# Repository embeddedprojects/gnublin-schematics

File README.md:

gnublin-schematics
==================

GNUBLIN Schematic and Board Files

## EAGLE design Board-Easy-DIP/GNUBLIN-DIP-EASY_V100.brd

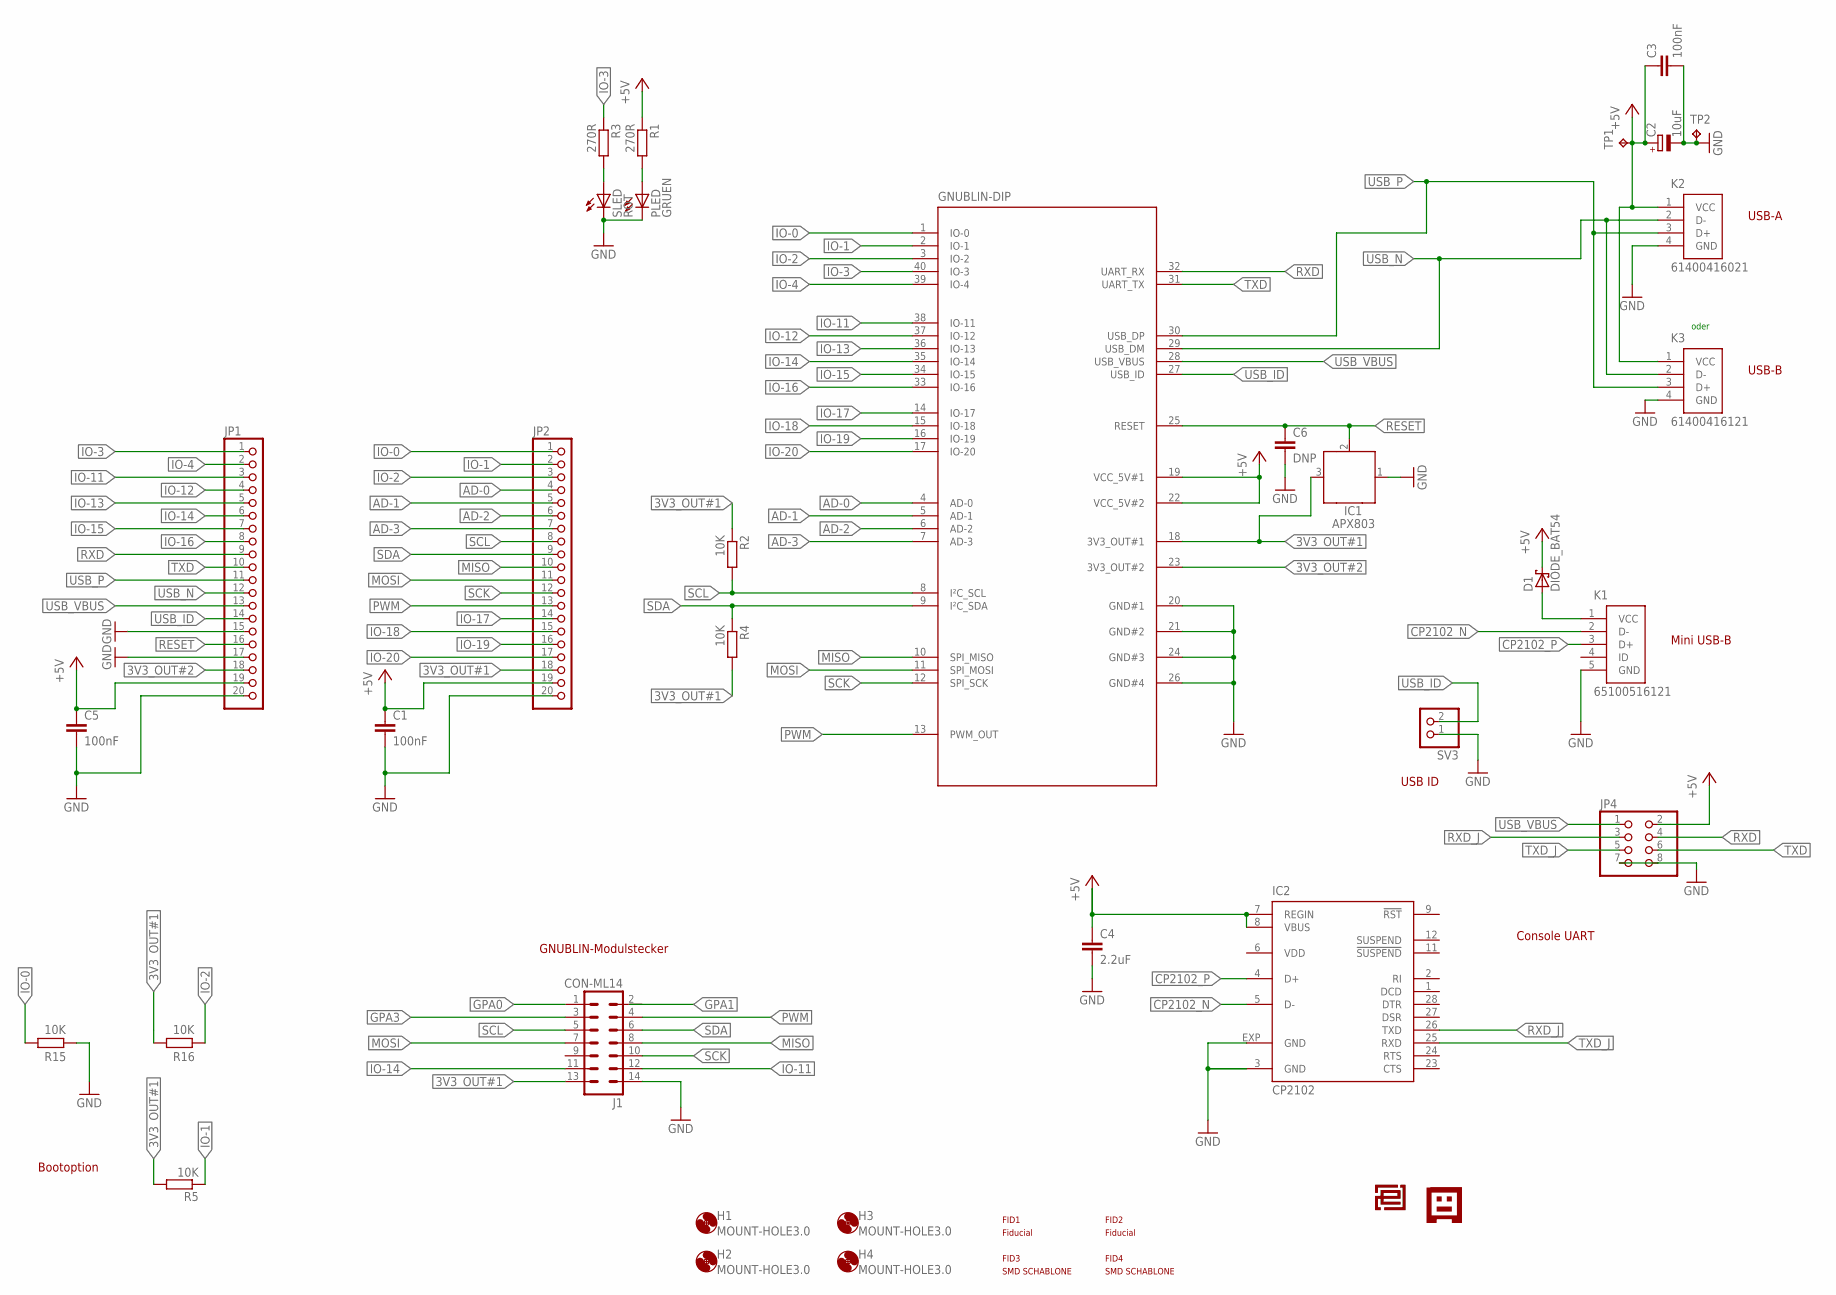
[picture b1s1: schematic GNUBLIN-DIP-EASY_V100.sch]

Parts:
C1, C3, C5: 100nF; C0805
C2: 10uF; D/7343-31R
C4: 2.2uF; C0805
C6: DNP; C0805
D1: DIODE_BAT54; SOT-23
FID1, FID2, FID3, FID4: PASSERMARKEN_FIDUCIAL
H1, H2, H3, H4: MOUNT-HOLE3.0; 3,0
IC1: APX803; SOT23
IC2: CP2102; MLP28
J1: CON-ML14; ML-14
JP1, JP2: PINHD-1X20; 1X20
JP4: PINHD-2X4; 2X04
K1: 65100516121
K2: 61400416021
K3: 61400416121
PLED: GRUEN; CHIPLED_0805
R1, R3: 270R; R0805
R2, R4, R5, R15, R16: 10K; R0805
SLED: ROT; CHIPLED_0805
SV3: PINHD-1X2; 1X02
TP1, TP2: TPB1,27; B1,27
U4: GNUBLIN-DIP; DIL40
U$1: GNUBLIN-LOGODRUCK; GNUBLINSIEBDRUCK
U$2: EPLOGOSIEB; EPLOGOSIEBDRUCK

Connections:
3V3_OUT#1: IC1.3 (VCC), J1.13, JP2.18, R2.1, R4.2, R5.2, R16.1, U4.18 (3V3_OUT#1)
3V3_OUT#2: JP1.18, U4.23 (3V3_OUT#2)
+5V: C1.1, C2.+, C3.1, C4.1, C5.1, D1.3 (C), IC2.7 (REGIN), IC2.8 (VBUS), JP1.19, JP2.19, JP4.2, K2.1 (VCC), K3.1 (VCC), R1.1, TP1.TP, U4.19 (VCC_5V#1), U4.22 (VCC_5V#2)
AD-0: JP2.4, U4.4 (AD-0)
AD-1: JP2.5, U4.5 (AD-1)
AD-2: JP2.6, U4.6 (AD-2)
AD-3: JP2.7, U4.7 (AD-3)
CP2102_N: IC2.5 (D-), K1.2 (D-)
CP2102_P: IC2.4 (D+), K1.3 (D+)
GND: C1.2, C2.-, C3.2, C4.2, C5.2, C6.2, IC1.1 (GND), IC2.3 (GND), IC2.EXP (GND), J1.14, JP1.15, JP1.17, JP1.20, JP2.20, JP4.7, JP4.8, K1.5 (GND), K2.4 (GND), K3.4 (GND), PLED.C, R15.2, SLED.C, SV3.1, TP2.TP, U4.20 (GND#1), U4.21 (GND#2), U4.24 (GND#3), U4.26 (GND#4)
GPA0: J1.1
GPA3: J1.3
IO-0: JP2.1, R15.1, U4.1 (IO-0)
IO-1: JP2.2, R5.1, U4.2 (IO-1)
IO-2: JP2.3, R16.2, U4.3 (IO-2)
IO-3: JP1.1, R3.1, U4.40 (IO-3)
IO-4: JP1.2, U4.39 (IO-4)
IO-11: J1.12, JP1.3, U4.38 (IO-11)
IO-12: JP1.4, U4.37 (IO-12)
IO-13: JP1.5, U4.36 (IO-13)
IO-14: J1.11, JP1.6, U4.35 (IO-14)
IO-15: JP1.7, U4.34 (IO-15)
IO-16: JP1.8, U4.33 (IO-16)
IO-17: JP2.14, U4.14 (IO-17)
IO-18: JP2.15, U4.15 (IO-18)
IO-19: JP2.16, U4.16 (IO-19)
IO-20: JP2.17, U4.17 (IO-20)
MISO: J1.8, JP2.10, U4.10 (SPI_MISO)
MOSI: J1.7, JP2.11, U4.11 (SPI_MOSI)
unnamed: R3.2, SLED.A
unnamed: D1.1 (A), K1.1 (VCC)
unnamed: PLED.A, R1.2
PWM: J1.4, JP2.13, U4.13 (PWM_OUT)
RESET: C6.1, IC1.2 (!RESET), JP1.16, U4.25 (RESET)
RXD: JP1.9, JP4.4, U4.32 (UART_RX)
RXD_J: IC2.26 (TXD), JP4.3
SCK: J1.10, JP2.12, U4.12 (SPI_SCK)
SCL: J1.5, JP2.8, R2.2, U4.8 (I²C_SCL)
SDA: J1.6, JP2.9, R4.1, U4.9 (I²C_SDA)
TXD: JP1.10, JP4.6, U4.31 (UART_TX)
TXD_J: IC2.25 (RXD), JP4.5
USB_ID: JP1.14, SV3.2, U4.27 (USB_ID)
USB_N: JP1.12, K2.2 (D-), K3.2 (D-), U4.29 (USB_DM)
USB_P: JP1.11, K2.3 (D+), K3.3 (D+), U4.30 (USB_DP)
USB_VBUS: JP1.13, JP4.1, U4.28 (USB_VBUS)
VDD: IC2.6 (VDD)

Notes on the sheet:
USB ID
Mini USB-B
USB-A
Bootoption
GNUBLIN-Modulstecker
Console UART
oder
USB-B

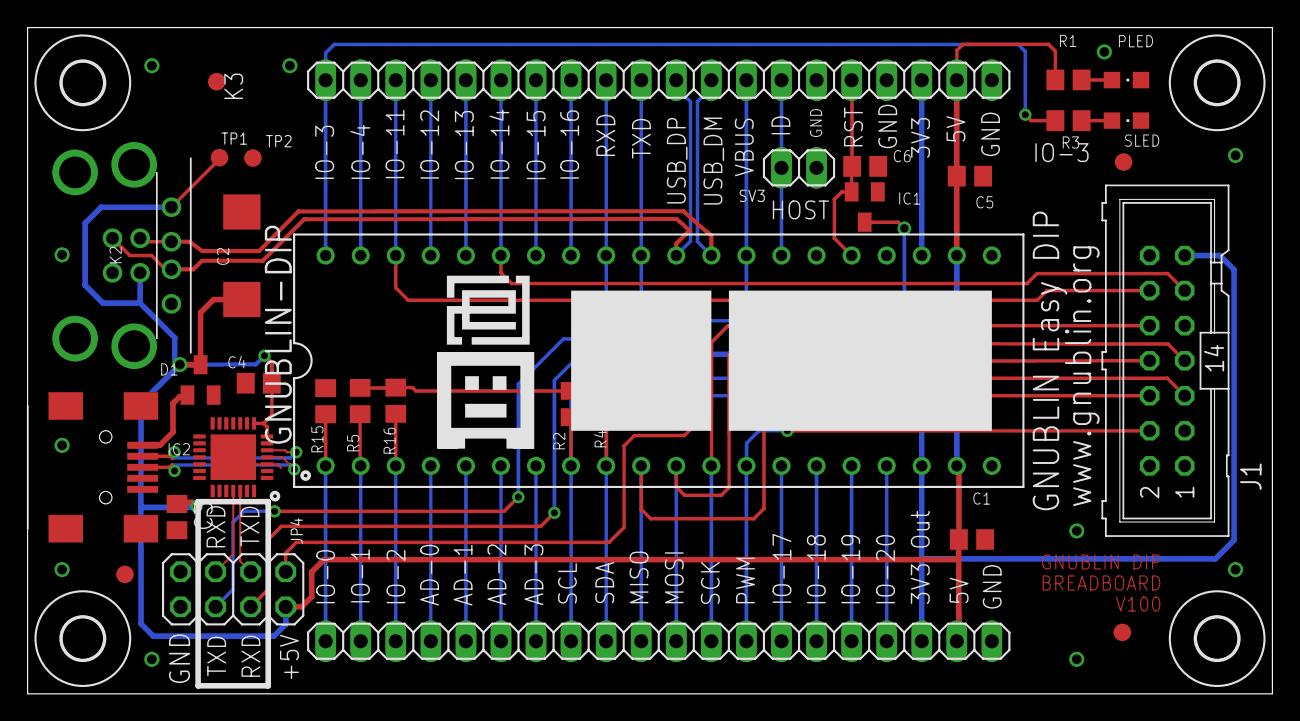
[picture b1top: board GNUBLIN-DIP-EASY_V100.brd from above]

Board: 2 copper layers, 90.2 x 48.3 mm, 39 parts (0 on the bottom side), 43 nets.

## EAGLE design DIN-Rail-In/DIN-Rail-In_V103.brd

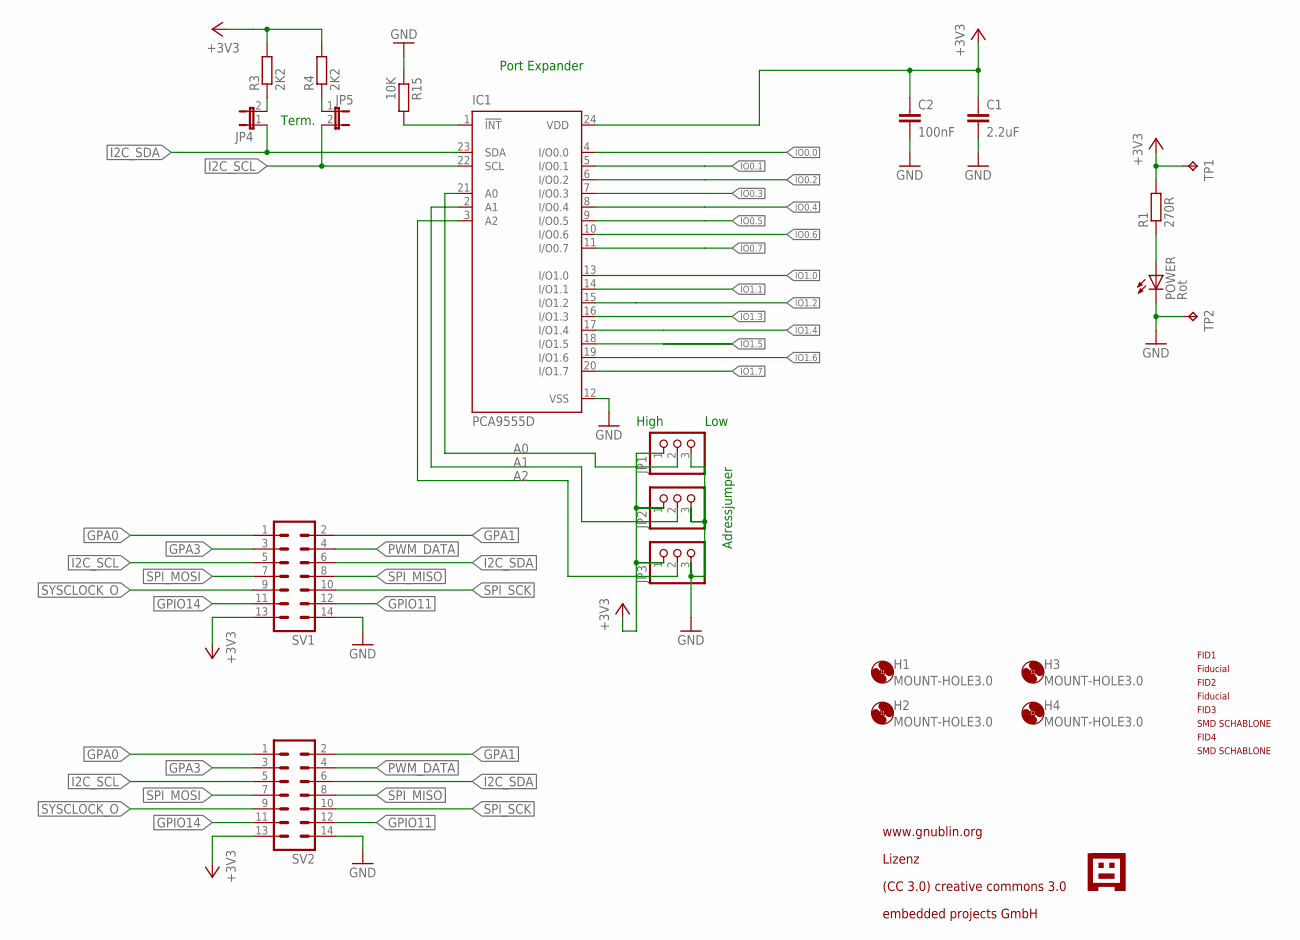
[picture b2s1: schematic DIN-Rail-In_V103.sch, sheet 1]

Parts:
C1: 2.2uF; C0805
C2: 100nF; C0805
FID1, FID2, FID3, FID4: PASSERMARKEN_FIDUCIAL
H1, H2, H3, H4: MOUNT-HOLE3.0; 3,0
IC1: PCA9555D; SO24
JP1, JP2, JP3: PINHD-1X3; 1X03
JP4, JP5: JP1E; JP1
POWER: Rot; CHIP-LED0805
R1: 270R; R0805
R3, R4: 2K2; R0805
R15: 10K; R0805
SV1, SV2: ML14
TP1, TP2: TPB1,27; B1,27
U$2: GNUBLINLOGOSIEB; GNUSIEBDRUCK

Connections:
!INT: IC1.1 (!INT), R15.2
+3V3: C1.1, C2.1, IC1.24 (VDD), JP1.1, JP2.1, JP3.1, R1.2, R3.2, R4.2, SV1.13, SV2.13, TP1.TP; also elsewhere on the board
A0: IC1.21 (A0), JP1.2
A1: IC1.2 (A1), JP2.2
A2: IC1.3 (A2), JP3.2
GND: C1.2, C2.2, IC1.12 (VSS), JP1.3, JP2.3, JP3.3, POWER.C, R15.1, SV1.14, SV2.14, TP2.TP; also elsewhere on the board
GPA0: SV1.1, SV2.1
GPA1: SV1.2, SV2.2
GPA3: SV1.3, SV2.3
GPIO11: SV1.12, SV2.12
GPIO14: SV1.11, SV2.11
I2C_SCL: IC1.22 (SCL), JP5.2, SV1.5, SV2.5
I2C_SDA: IC1.23 (SDA), JP4.1, SV1.6, SV2.6
IO0.0: IC1.4 (I/O0.0)
IO0.1: IC1.5 (I/O0.1)
IO0.2: IC1.6 (I/O0.2)
IO0.3: IC1.7 (I/O0.3)
IO0.4: IC1.8 (I/O0.4)
IO0.5: IC1.9 (I/O0.5)
IO0.6: IC1.10 (I/O0.6)
IO0.7: IC1.11 (I/O0.7)
IO1.0: IC1.13 (I/O1.0); also elsewhere on the board
IO1.1: IC1.14 (I/O1.1); also elsewhere on the board
IO1.2: IC1.15 (I/O1.2); also elsewhere on the board
IO1.3: IC1.16 (I/O1.3); also elsewhere on the board
IO1.4: IC1.17 (I/O1.4); also elsewhere on the board
IO1.5: IC1.18 (I/O1.5); also elsewhere on the board
IO1.6: IC1.19 (I/O1.6); also elsewhere on the board
IO1.7: IC1.20 (I/O1.7); also elsewhere on the board
unnamed: JP4.2, R3.1
unnamed: POWER.A, R1.1
unnamed: JP5.1, R4.1
PWM_DATA: SV1.4, SV2.4
SPI_MISO: SV1.8, SV2.8
SPI_MOSI: SV1.7, SV2.7
SPI_SCK: SV1.10, SV2.10
SYSCLOCK_O: SV1.9, SV2.9

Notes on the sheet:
Port Expander
Adressjumper
Term.
High
Low
www.gnublin.org
Lizenz
(CC 3.0) creative commons 3.0
embedded projects GmbH

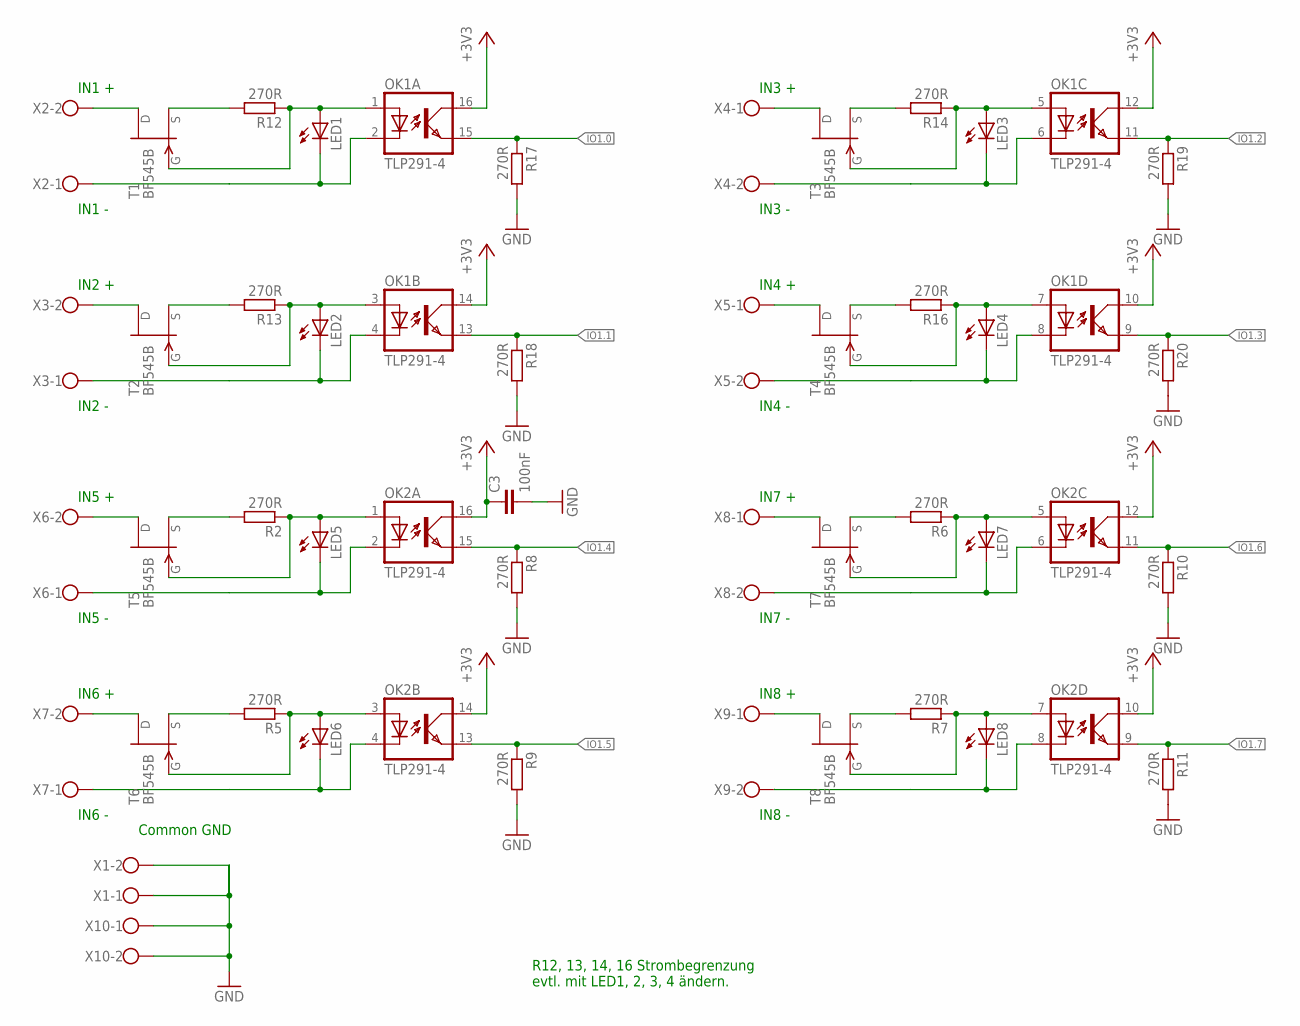
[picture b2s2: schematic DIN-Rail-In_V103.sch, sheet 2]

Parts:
C3: 100nF; C0805
LED1, LED2, LED3, LED4, LED5, LED6, LED7, LED8: LEDCHIPLED_0805; CHIPLED_0805
OK1, OK2: TLP291-4; MINI-FLAT-16
R2, R5, R6, R7, R8, R9, R10, R11, R12, R13, R14, R16, R17, R18, R19, R20: 270R; R0805
T1, T2, T3, T4, T5, T6, T7, T8: BF545B; SOT-23
X1, X2, X3, X4, X5, X6, X7, X8, X9, X10: W237-02P; W237-132

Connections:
+3V3: C3.1, OK1.10 (COL), OK1.12 (COL), OK1.14 (COL), OK1.16 (COL), OK2.10 (COL), OK2.12 (COL), OK2.14 (COL), OK2.16 (COL); also elsewhere on the board
GND: C3.2, R8.2, R9.2, R10.2, R11.2, R17.2, R18.2, R19.2, R20.2, X1.1, X1.2, X10.1, X10.2; also elsewhere on the board
IO1.0: OK1.15 (EMIT), R17.1; also elsewhere on the board
IO1.1: OK1.13 (EMIT), R18.1; also elsewhere on the board
IO1.2: OK1.11 (EMIT), R19.1; also elsewhere on the board
IO1.3: OK1.9 (EMIT), R20.1; also elsewhere on the board
IO1.4: OK2.15 (EMIT), R8.1; also elsewhere on the board
IO1.5: OK2.13 (EMIT), R9.1; also elsewhere on the board
IO1.6: OK2.11 (EMIT), R10.1; also elsewhere on the board
IO1.7: OK2.9 (EMIT), R11.1; also elsewhere on the board
unnamed: T1.2 (D), X2.2
unnamed: LED1.A, OK1.1 (A), R12.1, T1.3 (G)
unnamed: T5.2 (D), X6.2
unnamed: T2.2 (D), X3.2
unnamed: LED2.A, OK1.3 (A), R13.1, T2.3 (G)
unnamed: LED5.A, OK2.1 (A), R2.1, T5.3 (G)
unnamed: LED1.C, OK1.2 (C), X2.1
unnamed: T3.2 (D), X4.1
unnamed: LED3.A, OK1.5 (A), R14.1, T3.3 (G)
unnamed: T4.2 (D), X5.1
unnamed: LED4.A, OK1.7 (A), R16.1, T4.3 (G)
unnamed: T6.2 (D), X7.2
unnamed: LED2.C, OK1.4 (C), X3.1
unnamed: LED6.A, OK2.3 (A), R5.1, T6.3 (G)
unnamed: LED3.C, OK1.6 (C), X4.2
unnamed: LED4.C, OK1.8 (C), X5.2
unnamed: R12.2, T1.1 (S)
unnamed: T7.2 (D), X8.1
unnamed: R13.2, T2.1 (S)
unnamed: LED7.A, OK2.5 (A), R6.1, T7.3 (G)
unnamed: R14.2, T3.1 (S)
unnamed: T8.2 (D), X9.1
unnamed: R16.2, T4.1 (S)
unnamed: LED8.A, OK2.7 (A), R7.1, T8.3 (G)
unnamed: LED5.C, OK2.2 (C), X6.1
unnamed: LED6.C, OK2.4 (C), X7.1
unnamed: LED7.C, OK2.6 (C), X8.2
unnamed: LED8.C, OK2.8 (C), X9.2
unnamed: R2.2, T5.1 (S)
unnamed: R5.2, T6.1 (S)
unnamed: R6.2, T7.1 (S)
unnamed: R7.2, T8.1 (S)

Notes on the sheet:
IN1 +
IN1 -
IN2 +
IN2 -
IN3 +
IN3 -
IN4 +
IN4 -
Common GND
R12, 13, 14, 16 Strombegrenzung evtl. mit LED1, 2, 3, 4 ändern.
IN5 +
IN5 -
IN6 +
IN6 -
IN7 +
IN7 -
IN8 +
IN8 -

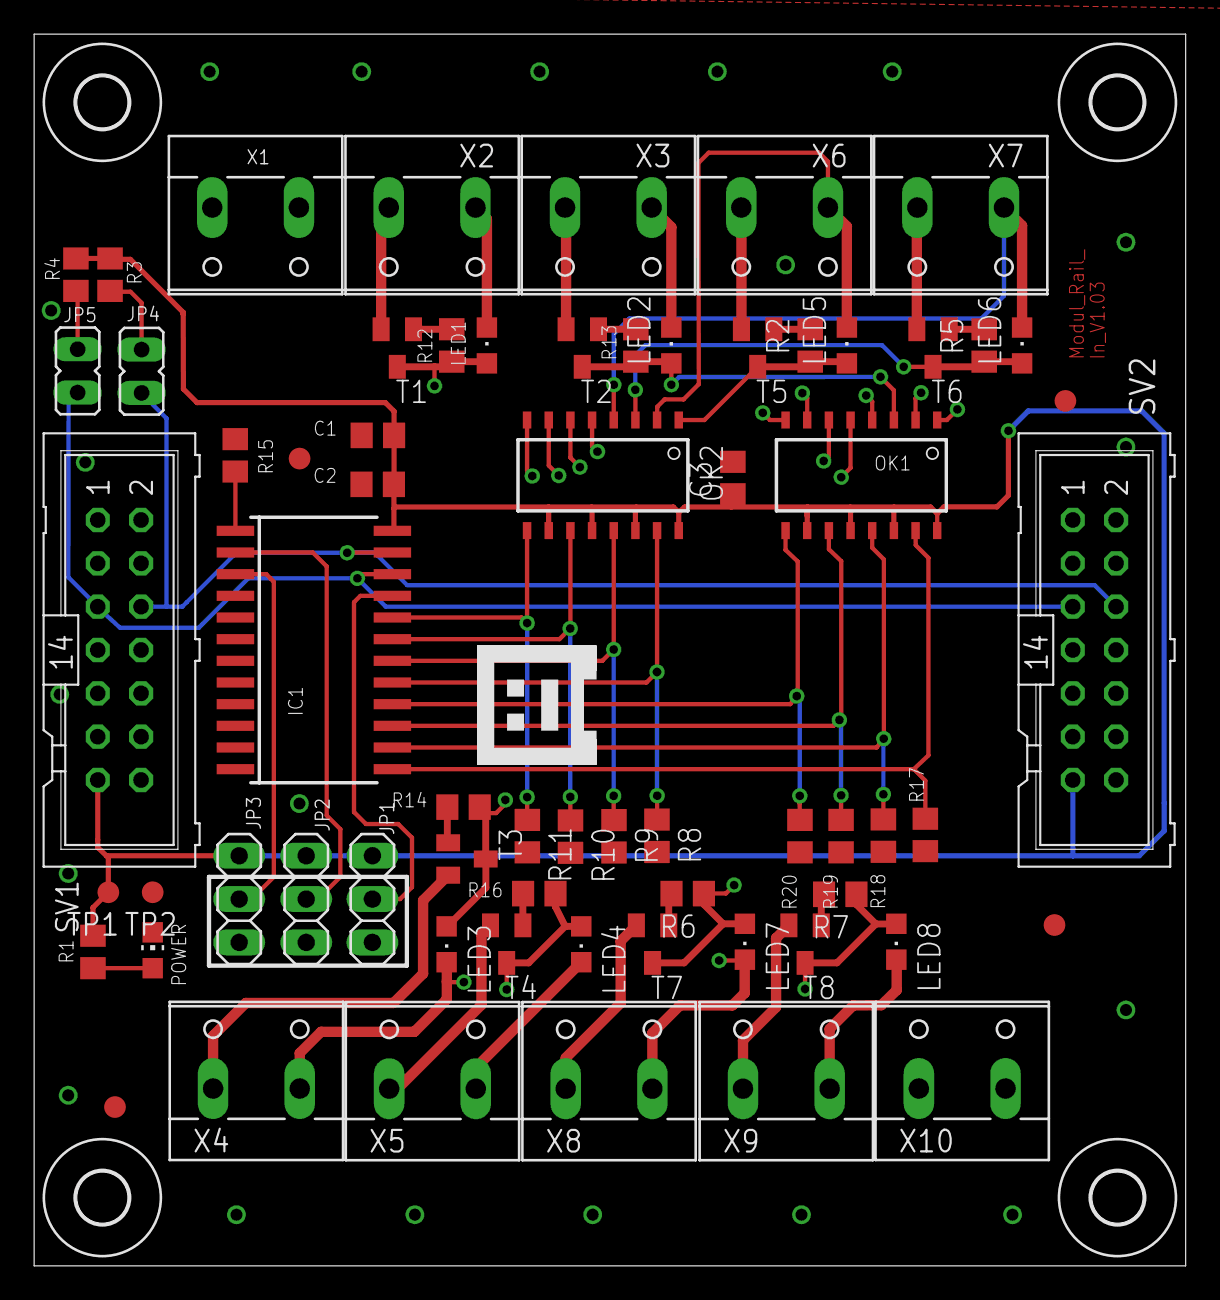
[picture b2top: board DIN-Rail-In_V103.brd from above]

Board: 4 copper layers, 67.5 x 72.2 mm, 71 parts (0 on the bottom side), 61 nets.

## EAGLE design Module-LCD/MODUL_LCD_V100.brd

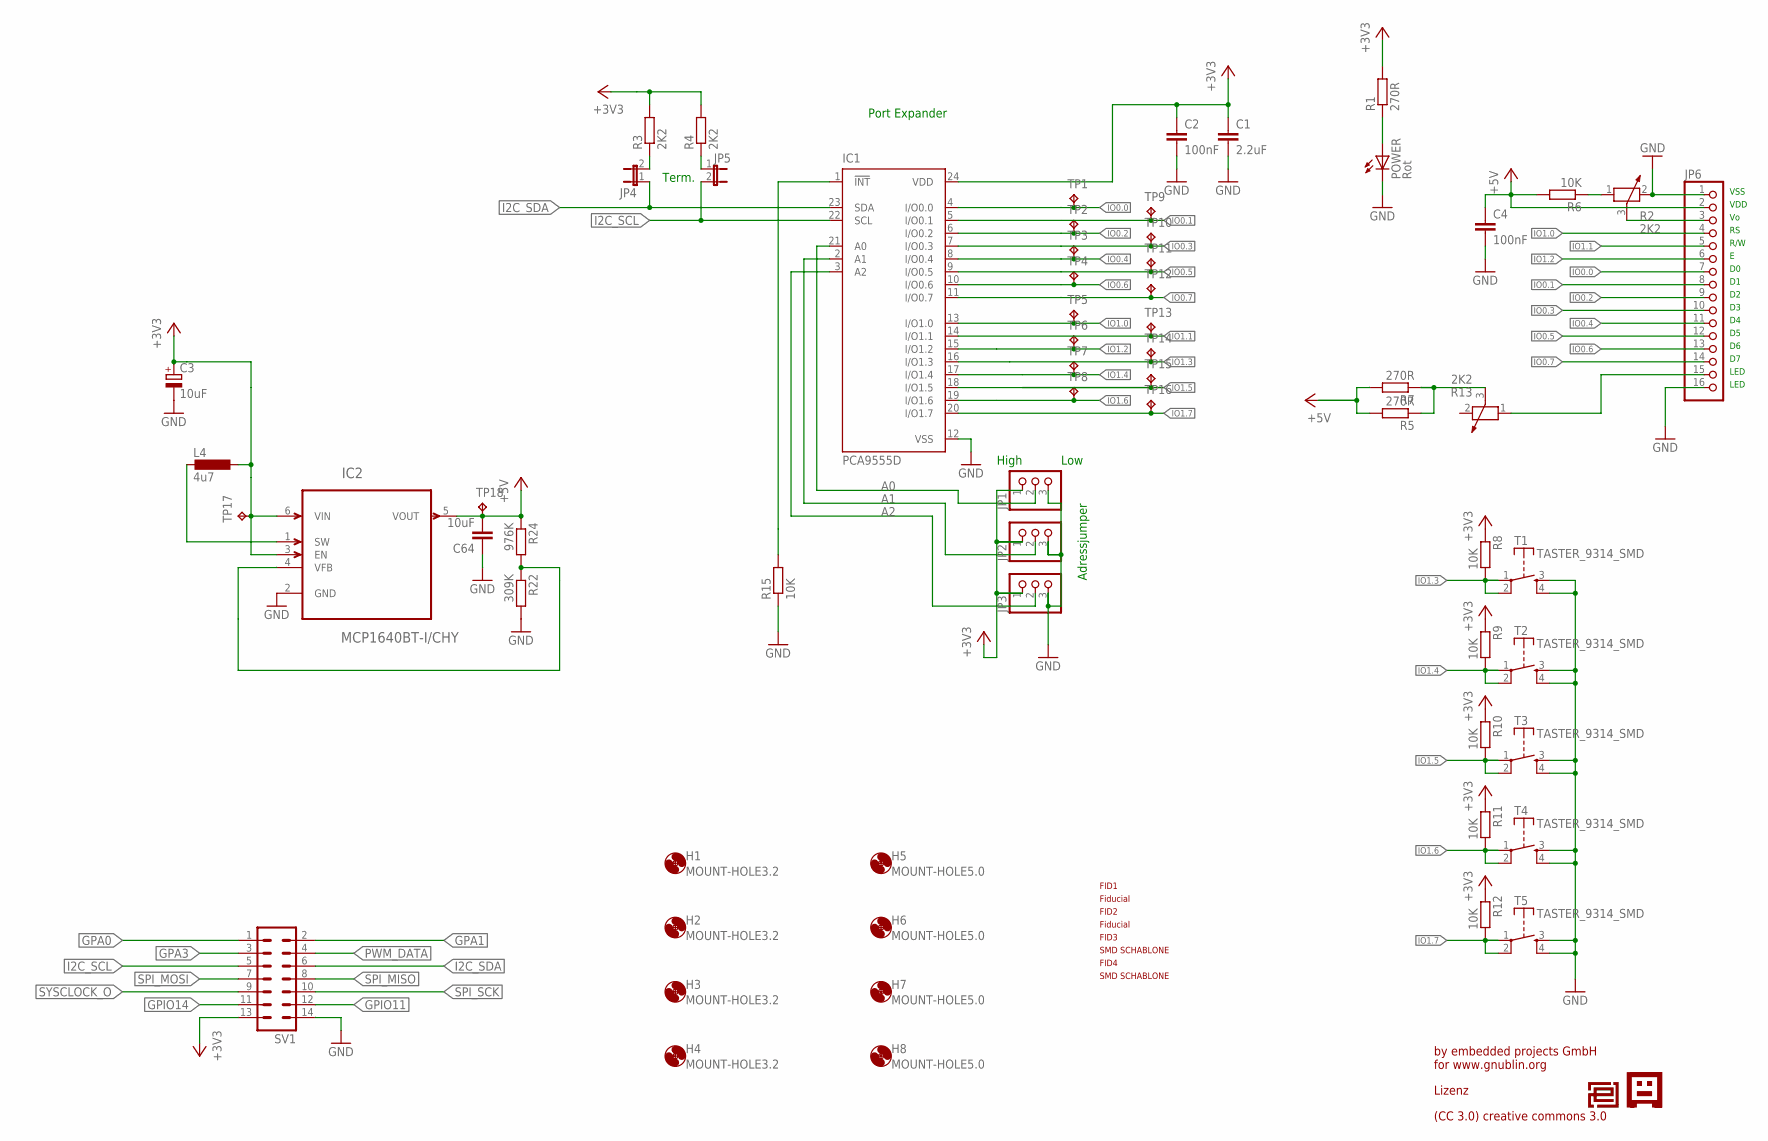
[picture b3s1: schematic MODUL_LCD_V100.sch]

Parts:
C1: 2.2uF; C0805
C2, C4: 100nF; C0805
C3: 10uF; SMC_D
C64: 10uF; C0805
FID1, FID2, FID3, FID4: PASSERMARKEN_FIDUCIAL
H1, H2, H3, H4: MOUNT-HOLE3.2; 3,2
H5, H6, H7, H8: MOUNT-HOLE5.0; 5,0
IC1: PCA9555D; SO24
IC2: MCP1640BT-I/CHY; SOT95P270X145-6N
JP1, JP2, JP3: PINHD-1X3; 1X03
JP4, JP5: JP1E; JP1
JP6: PINHD-1X16; 1X16
L4: 4u7; PSU3014
POWER: Rot; CHIP-LED0805
R1, R5, R7: 270R; R0805
R2, R13: 2K2; PT-10
R3, R4: 2K2; R0805
R6, R8, R9, R10, R11, R12, R15: 10K; R0805
R22: 309K; R0805
R24: 976K; R0805
SV1: ML14
T1, T2, T3, T4, T5: TASTER_9314_SMD; TASTER-9314_SMD
TP1, TP2, TP3, TP4, TP5, TP6, TP7, TP8, TP9, TP10, TP11, TP12, TP13, TP14, TP15, TP16, TP17, TP18: TPB1,27; B1,27
U$1: EPLOGOSIEB; EPLOGOSIEBDRUCK
U$2: GNUBLINLOGOSIEB; GNUSIEBDRUCK

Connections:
!INT: IC1.1 (!INT), R15.2
+3V3: C1.1, C2.1, C3.+, IC1.24 (VDD), IC2.3 (EN), IC2.6 (VIN), JP1.1, JP2.1, JP3.1, L4.2, R1.2, R3.2, R4.2, R8.1, R9.1, R10.1, R11.1, R12.1, SV1.13, TP17.TP
+5V: C4.1, C64.2, IC2.5 (VOUT), JP6.2, R5.2, R6.2, R7.2, R24.1, TP18.TP
A0: IC1.21 (A0), JP1.2
A1: IC1.2 (A1), JP2.2
A2: IC1.3 (A2), JP3.2
ENABLE_5V: IC2.1 (SW), L4.1
GND: C1.2, C2.2, C3.-, C4.2, C64.1, IC1.12 (VSS), IC2.2 (GND), JP1.3, JP2.3, JP3.3, JP6.1, JP6.16, POWER.C, R2.2, R15.1, R22.2, SV1.14, T1.3 (S), T1.4 (S), T2.3 (S), T2.4 (S), T3.3 (S), T3.4 (S), T4.3 (S), T4.4 (S), T5.3 (S), T5.4 (S)
GPA0: SV1.1
GPA1: SV1.2
GPA3: SV1.3
GPIO11: SV1.12
GPIO14: SV1.11
I2C_SCL: IC1.22 (SCL), JP5.2, SV1.5
I2C_SDA: IC1.23 (SDA), JP4.1, SV1.6
IO0.0: IC1.4 (I/O0.0), JP6.7, TP1.TP
IO0.1: IC1.5 (I/O0.1), JP6.8, TP9.TP
IO0.2: IC1.6 (I/O0.2), JP6.9, TP2.TP
IO0.3: IC1.7 (I/O0.3), JP6.10, TP10.TP
IO0.4: IC1.8 (I/O0.4), JP6.11, TP3.TP
IO0.5: IC1.9 (I/O0.5), JP6.12, TP11.TP
IO0.6: IC1.10 (I/O0.6), JP6.13, TP4.TP
IO0.7: IC1.11 (I/O0.7), JP6.14, TP12.TP
IO1.0: IC1.13 (I/O1.0), JP6.4, TP5.TP
IO1.1: IC1.14 (I/O1.1), JP6.5, TP13.TP
IO1.2: IC1.15 (I/O1.2), JP6.6, TP6.TP
IO1.3: IC1.16 (I/O1.3), R8.2, T1.1, T1.2, TP14.TP
IO1.4: IC1.17 (I/O1.4), R9.2, T2.1, T2.2, TP7.TP
IO1.5: IC1.18 (I/O1.5), R10.2, T3.1, T3.2, TP15.TP
IO1.6: IC1.19 (I/O1.6), R11.2, T4.1, T4.2, TP8.TP
IO1.7: IC1.20 (I/O1.7), R12.2, T5.1, T5.2, TP16.TP
unnamed: JP4.2, R3.1
unnamed: POWER.A, R1.1
unnamed: R2.1, R6.1
unnamed: JP6.15, R13.1
unnamed: JP5.1, R4.1
unnamed: R5.1, R7.1, R13.3
unnamed: IC2.4 (VFB), R22.1, R24.2
PWM_DATA: SV1.4
SPI_MISO: SV1.8
SPI_MOSI: SV1.7
SPI_SCK: SV1.10
SYSCLOCK_O: SV1.9
VO: JP6.3, R2.3

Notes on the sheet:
Port Expander
Adressjumper
Term.
High
Low
by embedded projects GmbH for www.gnublin.org
Lizenz
(CC 3.0) creative commons 3.0
VSS
VDD
R/W
LED

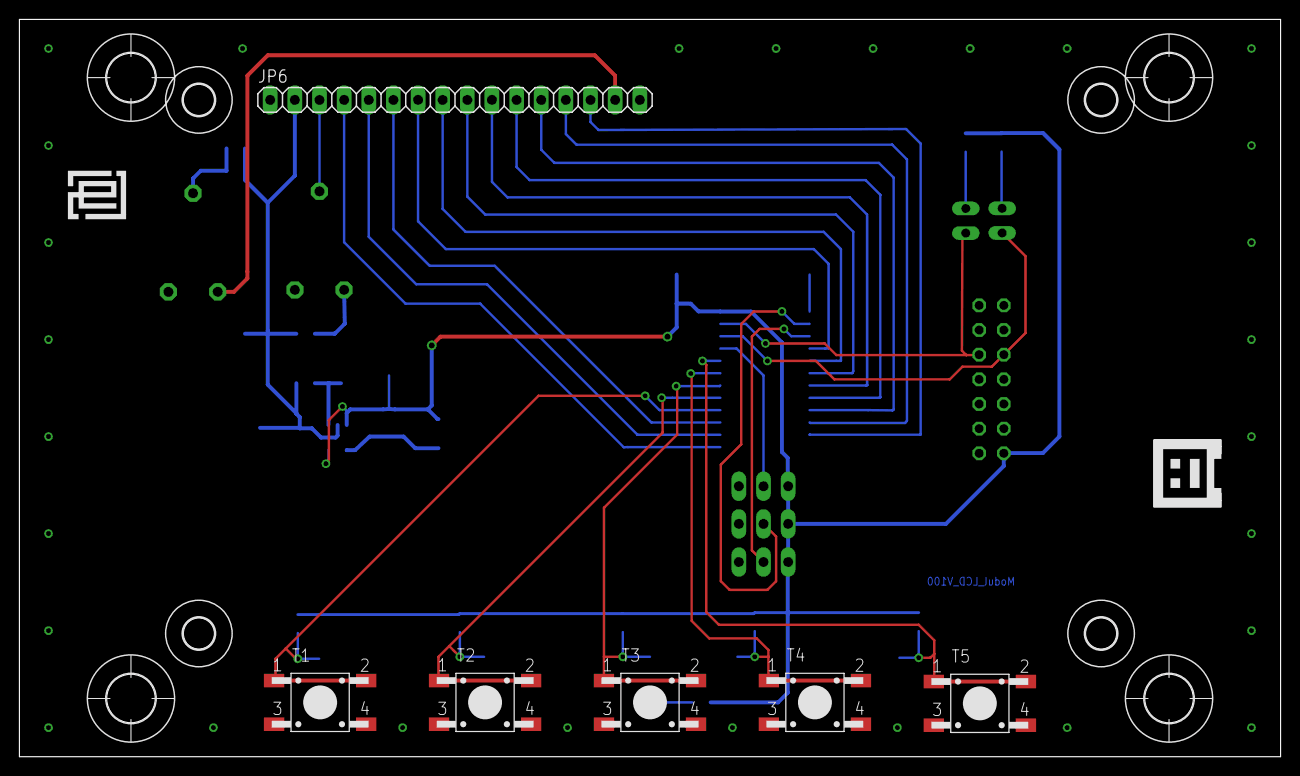
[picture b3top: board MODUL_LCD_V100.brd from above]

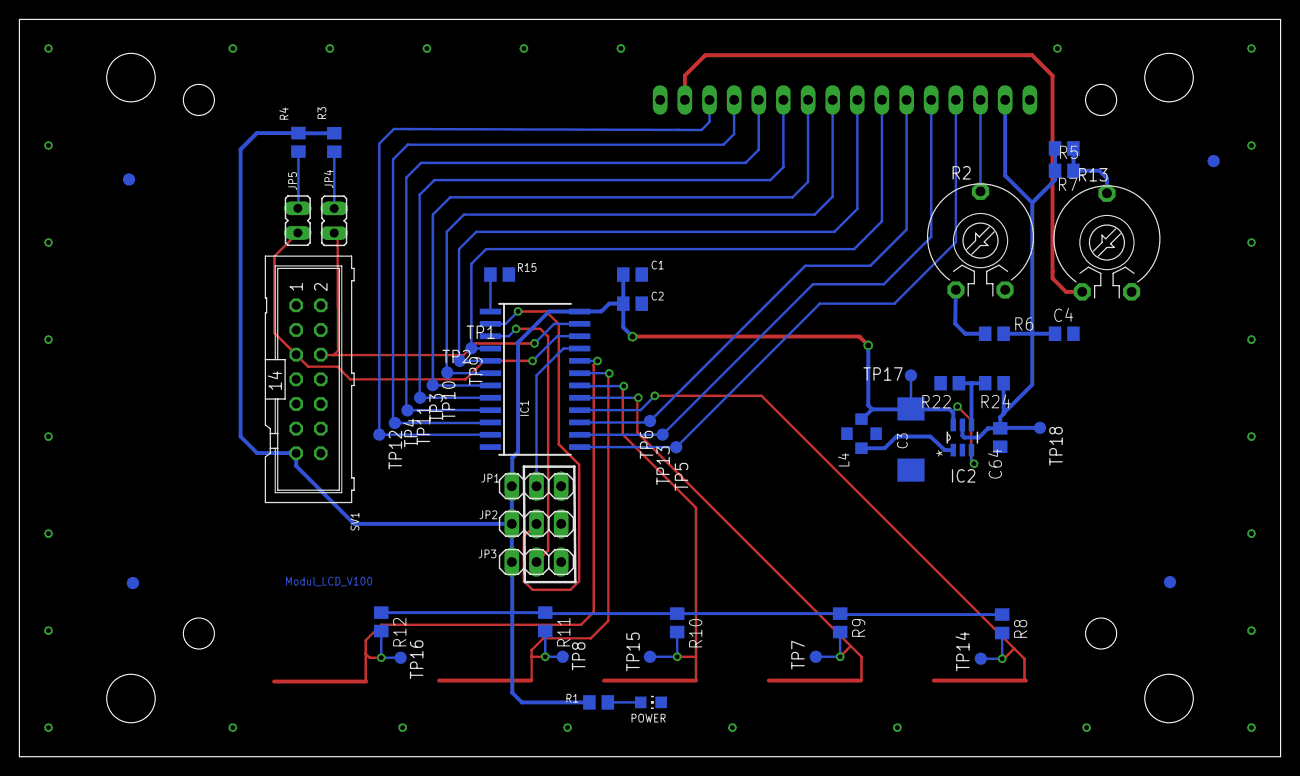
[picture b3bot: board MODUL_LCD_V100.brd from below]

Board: 2 copper layers, 130.0 x 76.0 mm, 69 parts (53 on the bottom side), 34 nets.

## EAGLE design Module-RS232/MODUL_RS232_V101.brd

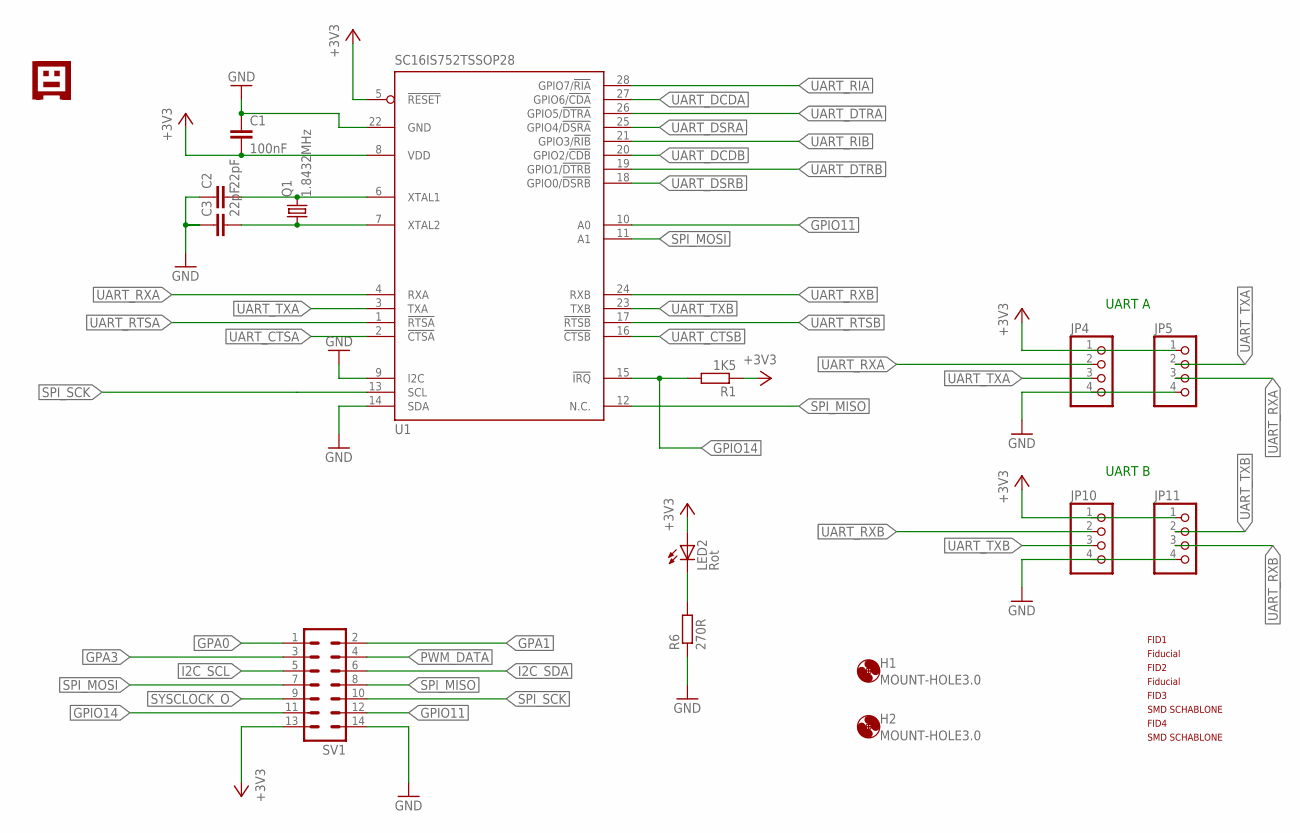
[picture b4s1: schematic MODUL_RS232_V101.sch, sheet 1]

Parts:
C1: 100nF; C0805
C2, C3: 22pF; C0805
FID1, FID2, FID3, FID4: PASSERMARKEN_FIDUCIAL
H1, H2: MOUNT-HOLE3.0; 3,0
JP4, JP5, JP10, JP11: PINHD-1X4; 1X04
LED2: Rot; CHIP-LED0805
Q1: 1.8432MHz; HC49UP
R1: 1K5; R0805
R6: 270R; R0805
SV1: ML14
U1: SC16IS752TSSOP28; TSSOP28; FARNELL 2101309
U$2: GNUBLINLOGOSIEB; GNUSIEBDRUCK

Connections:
+3V3: C1.2, JP4.1, JP5.1, JP10.1, JP11.1, LED2.A, R1.1, SV1.13, U1.5 (!RESET), U1.8 (VDD); also elsewhere on the board
GND: C1.1, C2.1, C3.1, JP4.4, JP5.4, JP10.4, JP11.4, R6.1, SV1.14, U1.9 (I2C), U1.14 (SDA), U1.22 (GND); also elsewhere on the board
GPA0: SV1.1
GPA1: SV1.2
GPA3: SV1.3
GPIO11: SV1.12, U1.10 (A0)
GPIO14: R1.2, SV1.11, U1.15 (!IRQ)
I2C_SCL: SV1.5
I2C_SDA: SV1.6
unnamed: C2.2, Q1.2, U1.6 (XTAL1)
unnamed: C3.2, Q1.1, U1.7 (XTAL2)
unnamed: LED2.C, R6.2
PWM_DATA: SV1.4
SPI_MISO: SV1.8, U1.12 (N.C.)
SPI_MOSI: SV1.7, U1.11 (A1)
SPI_SCK: SV1.10, U1.13 (SCL)
SYSCLOCK_O: SV1.9
UART_CTSA: U1.2 (!CTSA); also elsewhere on the board
UART_CTSB: U1.16 (!CTSB); also elsewhere on the board
UART_DCDA: U1.27 (GPIO6/!CDA); also elsewhere on the board
UART_DCDB: U1.20 (GPIO2/!CDB); also elsewhere on the board
UART_DSRA: U1.25 (GPIO4/!DSRA); also elsewhere on the board
UART_DSRB: U1.18 (GPIO0/!DSRB); also elsewhere on the board
UART_DTRA: U1.26 (GPIO5/!DTRA); also elsewhere on the board
UART_DTRB: U1.19 (GPIO1/!DTRB); also elsewhere on the board
UART_RIA: U1.28 (GPIO7/!RIA); also elsewhere on the board
UART_RIB: U1.21 (GPIO3/!RIB); also elsewhere on the board
UART_RTSA: U1.1 (!RTSA); also elsewhere on the board
UART_RTSB: U1.17 (!RTSB); also elsewhere on the board
UART_RXA: JP4.2, JP5.3, U1.4 (RXA); also elsewhere on the board
UART_RXB: JP10.2, JP11.3, U1.24 (RXB); also elsewhere on the board
UART_TXA: JP4.3, JP5.2, U1.3 (TXA); also elsewhere on the board
UART_TXB: JP10.3, JP11.2, U1.23 (TXB); also elsewhere on the board

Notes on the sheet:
UART A
UART B

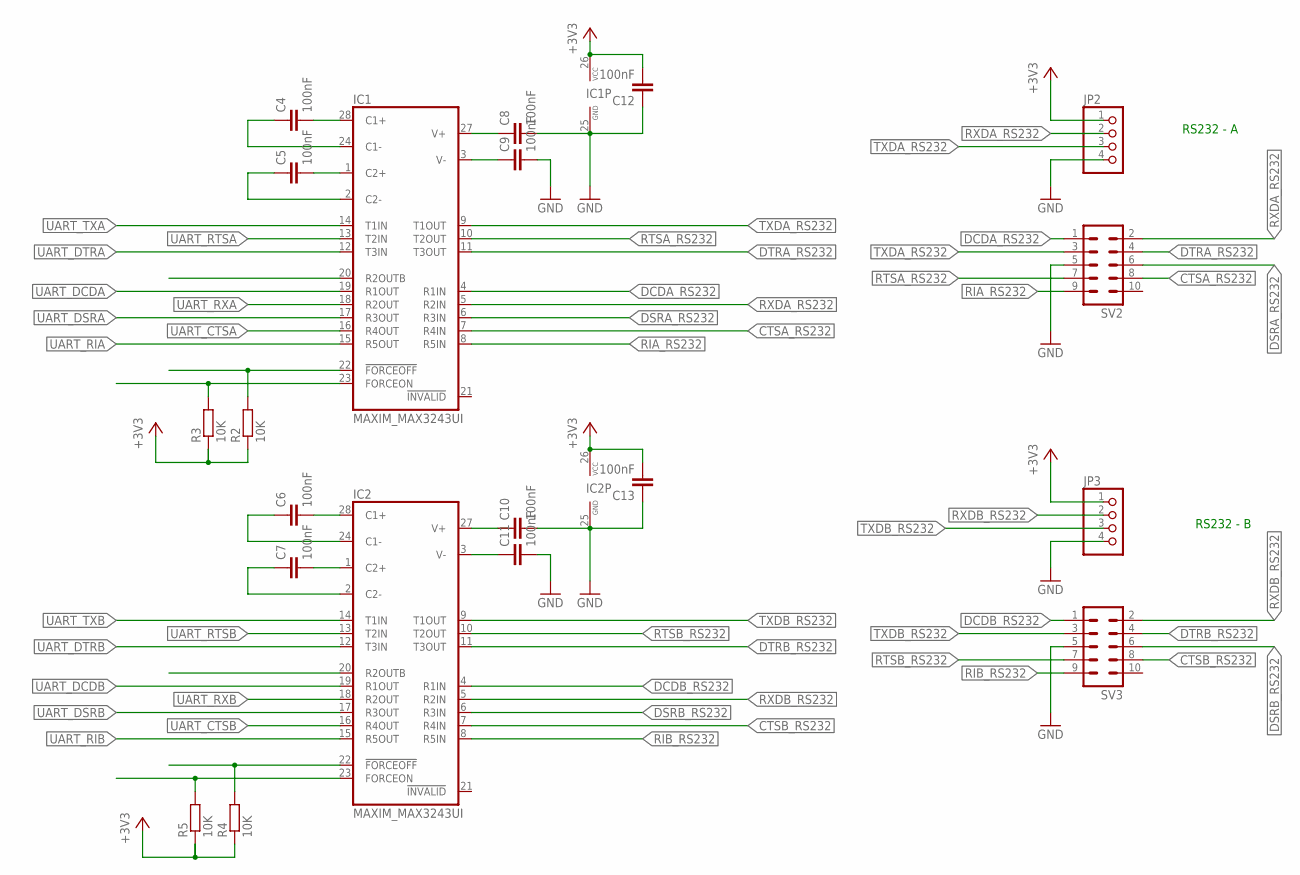
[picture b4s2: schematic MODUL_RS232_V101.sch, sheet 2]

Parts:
C4, C5, C6, C7, C8, C9, C10, C11, C12, C13: 100nF; C0805
IC1, IC2: MAXIM_MAX3243UI; MAXIM_TSSOP28
JP2, JP3: PINHD-1X4; 1X04
R2, R3, R4, R5: 10K; R0805
SV2, SV3: ML10

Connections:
+3V3: C12.2, C13.2, IC1.26 (VCC), IC2.26 (VCC), JP2.1, JP3.1, R2.1, R3.1, R4.1, R5.1; also elsewhere on the board
CTSA_RS232: IC1.7 (R4IN), SV2.8
CTSB_RS232: IC2.7 (R4IN), SV3.8
DCDA_RS232: IC1.4 (R1IN), SV2.1
DCDB_RS232: IC2.4 (R1IN), SV3.1
DSRA_RS232: IC1.6 (R3IN), SV2.6
DSRB_RS232: IC2.6 (R3IN), SV3.6
DTRA_RS232: IC1.11 (T3OUT), SV2.4
DTRB_RS232: IC2.11 (T3OUT), SV3.4
GND: C8.2, C9.2, C10.2, C11.2, C12.1, C13.1, IC1.25 (GND), IC2.25 (GND), JP2.4, JP3.4, SV2.5, SV3.5; also elsewhere on the board
unnamed: C4.2, IC1.28 (C1+)
unnamed: C5.2, IC1.1 (C2+)
unnamed: C4.1, IC1.24 (C1-)
unnamed: C5.1, IC1.2 (C2-)
unnamed: C6.2, IC2.28 (C1+)
unnamed: C7.2, IC2.1 (C2+)
unnamed: C6.1, IC2.24 (C1-)
unnamed: C7.1, IC2.2 (C2-)
unnamed: C8.1, IC1.27 (V+)
unnamed: C9.1, IC1.3 (V-)
unnamed: C10.1, IC2.27 (V+)
unnamed: C11.1, IC2.3 (V-)
unnamed: IC1.22 (!FORCEOFF), R2.2
unnamed: IC1.23 (FORCEON), R3.2
unnamed: IC2.22 (!FORCEOFF), R4.2
unnamed: IC2.23 (FORCEON), R5.2
RIA_RS232: IC1.8 (R5IN), SV2.9
RIB_RS232: IC2.8 (R5IN), SV3.9
RTSA_RS232: IC1.10 (T2OUT), SV2.7
RTSB_RS232: IC2.10 (T2OUT), SV3.7
RXDA_RS232: IC1.5 (R2IN), JP2.2, SV2.2
RXDB_RS232: IC2.5 (R2IN), JP3.2, SV3.2
TXDA_RS232: IC1.9 (T1OUT), JP2.3, SV2.3
TXDB_RS232: IC2.9 (T1OUT), JP3.3, SV3.3
UART_CTSA: IC1.16 (R4OUT); also elsewhere on the board
UART_CTSB: IC2.16 (R4OUT); also elsewhere on the board
UART_DCDA: IC1.19 (R1OUT); also elsewhere on the board
UART_DCDB: IC2.19 (R1OUT); also elsewhere on the board
UART_DSRA: IC1.17 (R3OUT); also elsewhere on the board
UART_DSRB: IC2.17 (R3OUT); also elsewhere on the board
UART_DTRA: IC1.12 (T3IN); also elsewhere on the board
UART_DTRB: IC2.12 (T3IN); also elsewhere on the board
UART_RIA: IC1.15 (R5OUT); also elsewhere on the board
UART_RIB: IC2.15 (R5OUT); also elsewhere on the board
UART_RTSA: IC1.13 (T2IN); also elsewhere on the board
UART_RTSB: IC2.13 (T2IN); also elsewhere on the board
UART_RXA: IC1.18 (R2OUT); also elsewhere on the board
UART_RXB: IC2.18 (R2OUT); also elsewhere on the board
UART_TXA: IC1.14 (T1IN); also elsewhere on the board
UART_TXB: IC2.14 (T1IN); also elsewhere on the board

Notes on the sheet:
RS232 - A
RS232 - B
